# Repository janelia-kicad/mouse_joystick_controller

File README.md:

- [About](#orgbfb5ebf)
- [Images](#org912eb98)
- [Schematic](#org0782f5f)
- [PCB](#org14a825d)
- [Bill of Materials](#orgcd1d3bb)
- [Notes](#org100e3b2)
- [Development](#orga0ec191)

    <!-- This file is generated automatically from metadata -->
    <!-- File edits may be overwritten! -->

# About

```markdown
- Project Name: mouse_joystick_controller
- Description: Janelia mouse joystick controller for the Dudman lab experiments.
- Version: 2.0
- Kicad Version: 7.0.11
- Release Date: 2024-08-05
- Creation Date: 2017-08-14
- License: BSD-3-Clause
- URL: https://github.com/janelia-kicad/mouse_joystick_controller
- Author: Peter Polidoro
- Email: peter@polidoro.io
- Copyright: 2024 Howard Hughes Medical Institute
- References:
  - https://www.kicad.org/
  - https://www.transducertechniques.com/rts-torque-sensor.aspx
  - https://placidindustries.com/products/brakes/magnetic-particle-brakes/magnetic-particle-brake-b5z/
  - https://www.newark.com/broadcom-limited/hedr-5421-ep111/encoder-incremental-2-ch/dp/58Y4773
  - https://www.linengineering.com/products/stepper-motors/hybrid-stepper-motors/208-series/208-13-01/WO-208-13-01D
  - https://www.pololu.com/product/2267
```

# Images

# Schematic

# PCB

# Bill of Materials

## Board

|    |
|--- |
|  |

## Supplemental

| Item | Description | Manufacturer Part Number | Manufacturer | Quantity |
|---- |----------- |------------------------ |------------ |-------- |

# Notes

## Actuators

### Stepper Motors

1.  Big

    SOYO SY42STH38-1684A

2.  Little

    Lin Engineering WO-208-13-01D-RO

### Brake

Placid Industries B5Z-24-1R Magnetic Particle Brake

-   Current control 0-0.049 A at 24 V

## Sensors

### Torque Sensor

Transducer Techniques RTS-5

-   wheatstone bridge

### Encoder

Newark HEDR-5421-EP111

-   Two channel quadrature

### Limit Switches

MiSUMi D2F-01FL

-   Normally open or normally closed

# Development

## Install Guix

[Install Guix](https://guix.gnu.org/manual/en/html_node/Binary-Installation.html)

## Edit metadata.org

    make metadata-edits

## Tangle metadata.org

    make metadata

## Edit project

    make kicad-edits
    exit

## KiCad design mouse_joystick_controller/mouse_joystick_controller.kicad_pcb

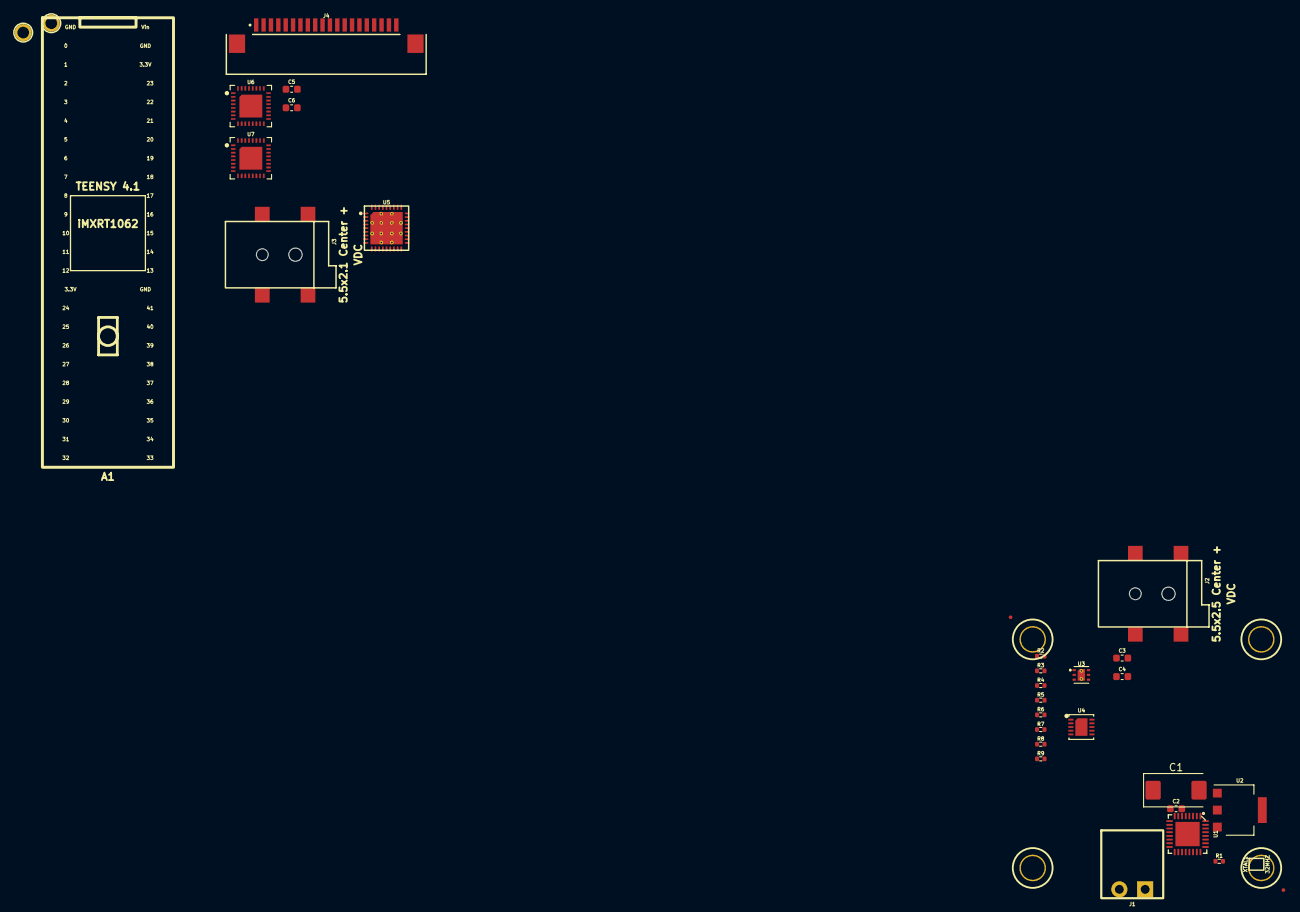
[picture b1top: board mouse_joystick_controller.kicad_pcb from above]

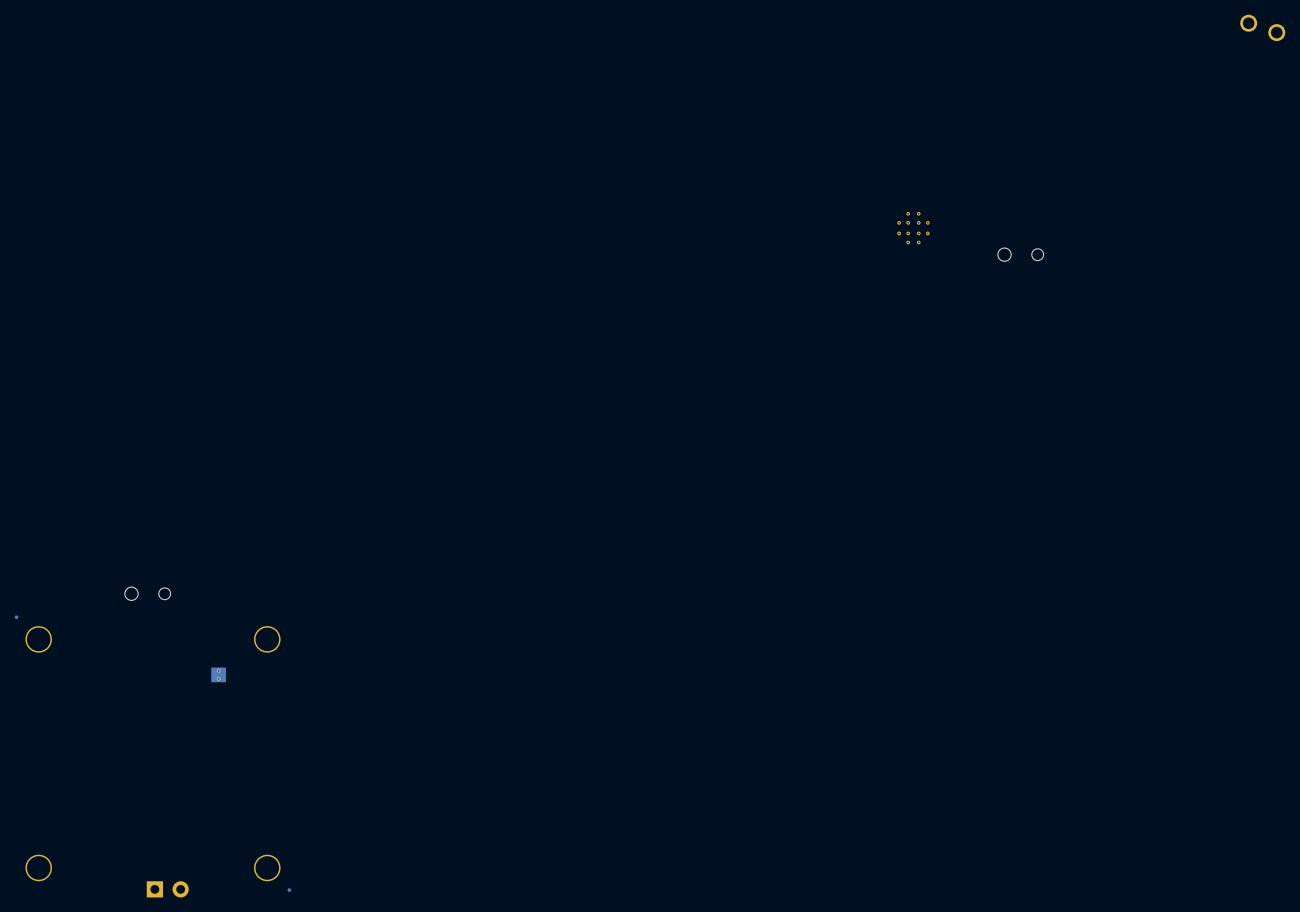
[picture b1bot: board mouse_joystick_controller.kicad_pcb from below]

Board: 4 copper layers, 38 parts (2 on the bottom side), 26 nets, no tracks yet.

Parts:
A1: TEENSY_4.1_PIN_RECEPTACLES
C1: 47uF_35V; CP_EIA-7343-43_Kemet-X
C2: 10uF_35V; C_0603_1608Metric
C3: 1uF_50V; C_0603_1608Metric
C4: 2.2uF_50V; C_0603_1608Metric
C5, C6: 0.1uF_50V; C_0603_1608Metric
FID1, FID2, FID3, FID4: FIDUCIAL_0.5mm_MASK1mm; FIDUCIAL_0.5mm_Mask1mm
H1, H2, H3, H4: MOUNTING_HOLE_3
J1: Conn_TERM_HDR_01x02_Pin_3.5MM_Horizontal; TERM_HDR_01x02_Pin_Horizontal_3.5MM_1844210
J2: 5.5x2.5_SMD_RA; CONN_54-00165
J3: 5.5x2.1_SMD_RA; CONN_54-00164
J4: Conn_FFC_20_Pin_1mm_bottom-ZF1-20-01-T-WT-TR; FFC_Samtec_ZF1-20-01-X-WT-Xx20-1MP_P1mm_Horizontal
PR0, PR1: Conn_Pin_Rcpt-0305-1-15; CONN_PIN_RCPT-0305-1-15
R1: 22; R_0402_1005Metric
R2, R3, R4, R5, R6, R7, R8, R9: 100; R_0402_1005Metric
U1: TMC429; QFN-32-1EP_5x5mm_P0.5mm_EP3.3x3.3mm
U2: NCR421ZX; SOT-223
U3: 3.3V_150MA; SON65P200X200X80-7N
U4: AD9837ACPZ-RL; DFN-10_DD_LIT-L
U5: PGA305ARHHR; RHH0036C
U6, U7: LVDS_4-4_HALF_DS91M040TSQE; DS91M040TSQE_NOPB
XTAL1: 32MHZ; XTAL_WURTH_IQX0-540

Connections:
/+24V: C3.1, J2.1, U3.6 (IN)
/GND: C3.2, C4.2, H1.1, H2.1, H3.1, H4.1, J2.2, J3.2, U3.3 (GND), U3.7 (PAD)
/brake/BRAKE+: C1.1, C2.1, J1.1
/brake/BRAKE-: J1.2, U2.4 (IOUT)
/brake/GND: C1.2, C2.2, R1.2, U2.3 (GND)
/brake/R_EXT: R1.1, U2.2 (REXT)
/motors/+3.3V: C5.1, C6.1, U6.10 (MDE), U6.11 (VDD), U6.12 (VDD), U6.14 (DE2), U6.25 (DE0), U6.27 (DE1), U6.29 (VDD), U6.30 (VDD), U7.10 (MDE), U7.11 (VDD), U7.12 (VDD), U7.25 (DE0), U7.27 (DE1), U7.29 (VDD), U7.30 (VDD)
/motors/+24V: J4.3, J4.4
/motors/GND: C5.2, C6.2, J4.1, J4.2, U6.31 (GND), U6.33 (PAD), U7.6 (DI2), U7.8 (DI3), U7.13 (~RE2), U7.15 (~RE3), U7.31 (GND), U7.33 (PAD)
/motors/UART_TX_ENABLE_0: U6.6 (DI2), U6.15 (~RE3), U6.16 (DE3)
/motors/driver_0/DIR_A: J4.17, R3.1, U6.21 (A1)
/motors/driver_0/DIR_B: J4.18, R3.2, U6.22 (B1)
/motors/driver_0/REFR_A: J4.5, R9.1, U7.17 (A3)
/motors/driver_0/REFR_B: J4.6, R9.2, U7.18 (B3)
/motors/driver_0/REF_A: J4.7, R8.1, U7.19 (A2)
/motors/driver_0/REF_B: J4.8, R8.2, U7.20 (B2)
/motors/driver_0/STANDBY_A: J4.9, R7.1, U7.21 (A1)
/motors/driver_0/STANDBY_B: J4.10, R7.2, U7.22 (B1)
/motors/driver_0/STEP_A: J4.19, R2.1, U6.23 (A0)
/motors/driver_0/STEP_B: J4.20, R2.2, U6.24 (B0)
/motors/driver_0/UART_A: J4.13, R5.1, U6.17 (A3)
/motors/driver_0/UART_B: J4.14, R5.2, U6.18 (B3)
/motors/driver_0/~DRIVER_ENABLE_A: J4.11, R6.1, U7.23 (A0)
/motors/driver_0/~DRIVER_ENABLE_B: J4.12, R6.2, U7.24 (B0)
/motors/driver_0/~UART_TX_ENABLE_A: J4.15, R4.1, U6.20 (B2)
/motors/driver_0/~UART_TX_ENABLE_B: J4.16, R4.2, U6.19 (A2)

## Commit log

2023-04-05 Initial commit.
2023-04-05 Update license
2023-04-05 Add some reference documentation
2023-04-13 Update reference links
2023-05-12 Add dds ic
2023-05-16 Add some driver components
2023-05-17 Add some sheets
2023-05-18 Add power jack
2023-05-18 Modify brake
2023-05-22 Add encoder, lickport, and torque_sensor sheets
2023-05-23 Add audio datasheet
2023-05-24 Rearrange sheets
2023-05-31 Add microcontroller sheet
2023-06-01 Modify brake circuit
2023-06-02 Kicad 7.0.2 -> 7.0.5
2023-06-02 Change brake circuitry again
2023-06-05 Update channels
2023-06-05 Add barrel jack connectors
2023-06-06 Add DDS chip in audio sheet
2023-06-07 power_enable -> standby
2023-06-08 Remove teensy component
2023-06-09 Test pin rcpt
2023-07-12 Move standby pin
2023-08-03 packages3D -> 3dmodels
2024-02-02 KiCad 7.0.8 -> 7.0.10
2024-08-05 Update metadata
